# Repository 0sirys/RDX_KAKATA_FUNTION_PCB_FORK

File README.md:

# RDX_KAKATA_FUNTION_PCB
RDX_KAKATA_FUNTION_PCB es el repositorio de diseno PCB de la tarjeta de control de funciones del proyecto RDX para la NASA

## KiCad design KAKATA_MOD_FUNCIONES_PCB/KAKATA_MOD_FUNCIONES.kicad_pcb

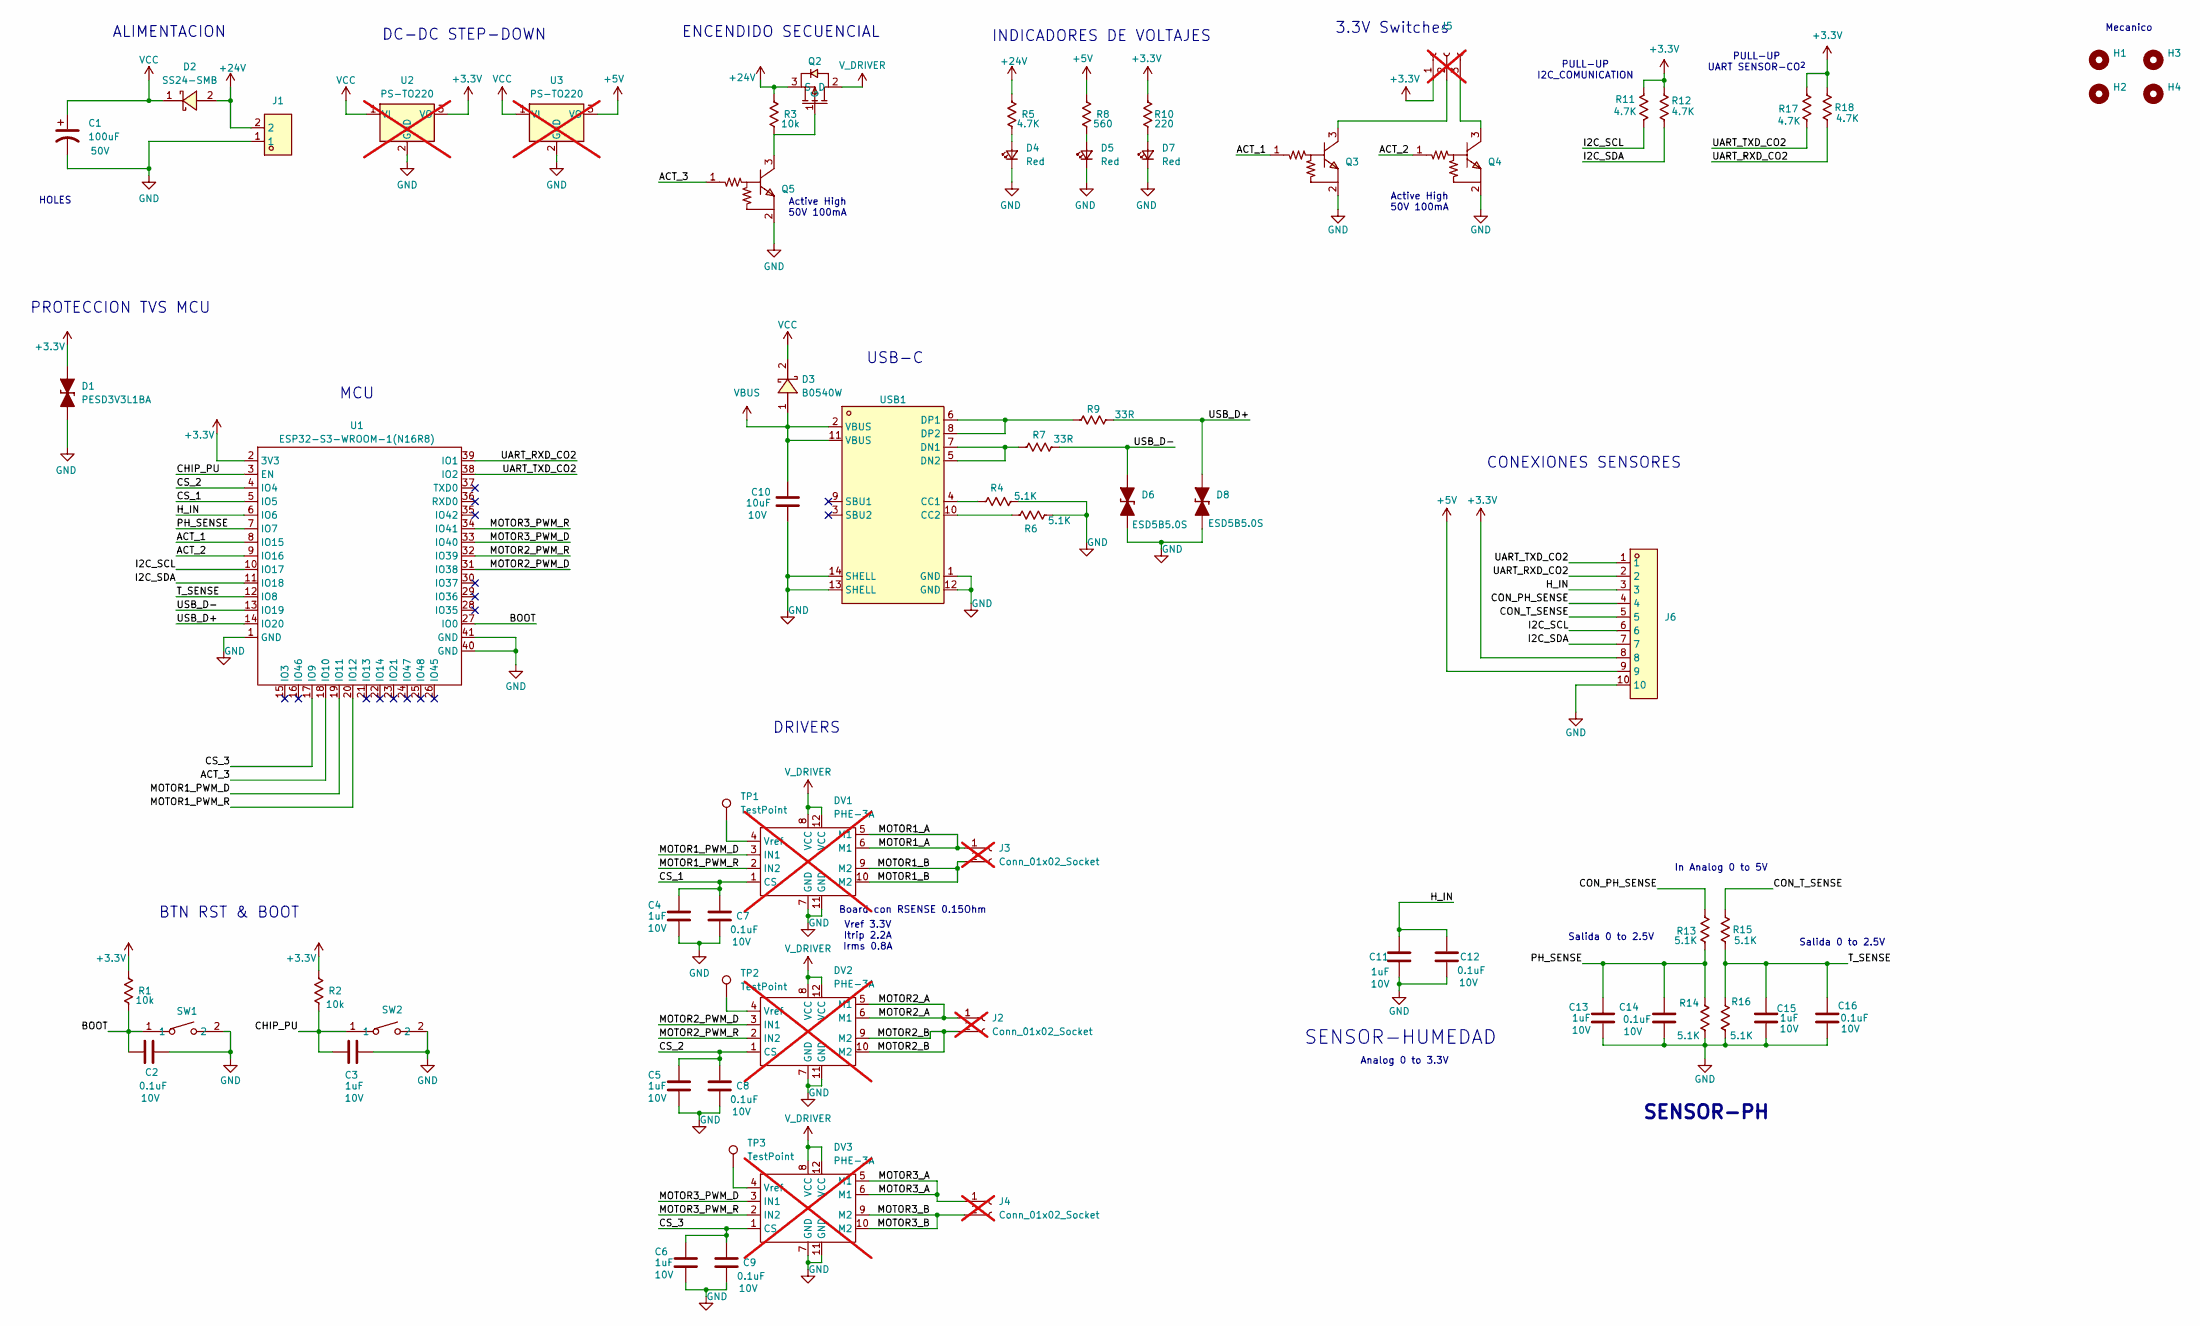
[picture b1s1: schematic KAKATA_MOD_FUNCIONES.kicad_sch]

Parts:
C1: 100uF; CAP-SMD_BD6.3-L6.6-W6.6-LS7.2-FD; LCSC Part C3151829
C2, C7, C8, C9, C12, C14, C16: 0.1uF; C0603; Voltage 10V; LCSC Part C14663
C3, C4, C5, C6, C11, C13, C15: 1uF; C0603; Voltage 10V; LCSC Part C113807
C10: 10uF; C0805; Voltage 10V; LCSC Part C88484
D1: PESD3V3L1BA; D_SOD-323
D2: SS24-SMB; SMB_L4.3-W3.6-LS5.3-RD; MPN SS24-SMB; LCSC Part C908683
D3: B0540W; SOD-123_L2.7-W1.6-LS3.7-FD; MPN B0540W; LCSC Part C7420325
D4, D5, D7: Red; LED_0201_0603Metric_Pad0.64x0.40mm_HandSolder; LCSC Part C965799
D6, D8: ESD5B5.0S; D_SOD-523; LCSC Part C93623
DV1, DV2, DV3: PHE-3A; not fitted
H1, H2, H3, H4: MountingHole; MountingHole_2.2mm_M2
J1: DB128L-5.08-2P-BK-S; CONN-TH_2P-P5.08_DB128L-5.08-2P-BK-S; LCSC Part C430601
J2, J3, J4: Conn_01x02_Socket; Molex_KK-254_AE-6410-02A_1x02_P2.54mm_Vertical; not fitted
J5: Conn_01x03_Socket; Molex_KK-254_AE-6410-03A_1x03_P2.54mm_Vertical; not fitted
J6: DB125-2.54-10P-GN; CONN-TH_DB125-2.54-10P-GN; LCSC Part C918128
Q2: AOD4185_C400894; TO-252-3_L6.6-W6.1-P4.57-LS9.9-BR-CW; MPN AOD4185; LCSC Part C400894
Q3, Q4, Q5: MMUN2215LT1G; SOT-23-3_L2.9-W1.3-P1.90-LS2.4-BR; MPN MMUN2215LT1G; LCSC Part C232613
R1, R2, R3: 10k; R0603; LCSC Part C98220
R4, R6, R13, R14, R15, R16: 5.1K; R0603; LCSC Part C105580
R5, R11, R12, R17, R18: 4.7K; R0603; LCSC Part C99782
R7, R9: 33R; R0603; LCSC Part C126353
R8: 560; R0603; LCSC Part C114629
R10: 220; R0603; LCSC Part C107696
SW1, SW2: TS-1088-AR02016; SW-SMD_L3.9-W3.0-P4.45; MPN TS-1088-AR02016; LCSC Part C720477
TP1, TP2, TP3: TestPoint; TestPoint_Pad_D2.0mm
U1: ESP32-S3-WROOM-1(N16R8); WIRELM-SMD_ESP32-S3-WROOM-1; LCSC Part C2913204
U2, U3: PS-TO220; PS-TO-220-3_Vertical; not fitted
USB1: TYPE-C 16PIN 2MD; USB-C-SMD_TYPE-C-6PIN-2MD-073; MPN TYPE-C 16PIN 2MD(073); LCSC Part C2765186

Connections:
+3.3V: D1.2 (A), J5.1, J6.8, R1.1, R2.1, R10.1, R11.1, R12.1, R17.1, R18.1, U1.2 (3V3), U2.3 (VO)
+5V: J6.9, R8.1, U3.3 (VO)
+24V: D2.2, J1.2, Q2.3 (S), R3.1, R5.1
/ACT_1: Q3.1, U1.8 (IO15)
/ACT_2: Q4.1, U1.9 (IO16)
/ACT_3: Q5.1, U1.18 (IO10)
/BOOT: C2.1, R1.2, SW1.1, U1.27 (IO0)
/CHIP_PU: C3.2, R2.2, SW2.1, U1.3 (EN)
/CON_PH_SENSE: J6.4, R13.1
/CON_T_SENSE: J6.5, R15.1
/CS_1: C4.2, C7.1, DV1.1 (CS), U1.5 (IO5)
/CS_2: C5.2, C8.1, DV2.1 (CS), U1.4 (IO4)
/CS_3: C6.2, C9.1, DV3.1 (CS), U1.17 (IO9)
/H_IN: C11.2, C12.1, J6.3, U1.6 (IO6)
/I2C_SCL: J6.6, R11.2, U1.10 (IO17)
/I2C_SDA: J6.7, R12.2, U1.11 (IO18)
/MOTOR1_A: DV1.5 (M1), DV1.6 (M1), J3.1
/MOTOR1_B: DV1.9 (M2), DV1.10 (M2), J3.2
/MOTOR1_PWM_D: DV1.3 (IN1), U1.19 (IO11)
/MOTOR1_PWM_R: DV1.2 (IN2), U1.20 (IO12)
/MOTOR2_A: DV2.5 (M1), DV2.6 (M1), J2.1
/MOTOR2_B: DV2.9 (M2), DV2.10 (M2), J2.2
/MOTOR2_PWM_D: DV2.3 (IN1), U1.31 (IO38)
/MOTOR2_PWM_R: DV2.2 (IN2), U1.32 (IO39)
/MOTOR3_A: DV3.5 (M1), DV3.6 (M1), J4.1
/MOTOR3_B: DV3.9 (M2), DV3.10 (M2), J4.2
/MOTOR3_PWM_D: DV3.3 (IN1), U1.33 (IO40)
/MOTOR3_PWM_R: DV3.2 (IN2), U1.34 (IO41)
/PH_SENSE: C13.2, C14.2, R13.2, R14.1, U1.7 (IO7)
/T_SENSE: C15.2, C16.2, R15.2, R16.1, U1.12 (IO8)
/UART_RXD_CO2: J6.2, R18.2, U1.39 (IO1)
/UART_TXD_CO2: J6.1, R17.2, U1.38 (IO2)
/USB_D+: D8.2 (A), R9.2, U1.14 (IO20)
/USB_D-: D6.2 (A), R7.2, U1.13 (IO19)
GND: C1.2, C2.2, C3.1, C4.1, C5.1, C6.1, C7.2, C8.2, C9.2, C10.2, C11.1, C12.2, C13.1, C14.1, C15.1, C16.1, D1.1 (K), D4.1 (K), D5.1 (K), D6.1 (K), D7.1 (K), D8.1 (K), DV1.7 (GND), DV1.11 (GND), DV2.7 (GND), DV2.11 (GND), DV3.7 (GND), DV3.11 (GND), J1.1, J6.10, Q3.2, Q4.2, Q5.2, R4.2, R6.2, R14.2, R16.2, SW1.2, SW2.2, U1.1 (GND), U1.40 (GND), U1.41 (GND), U2.2 (GND), U3.2 (GND), USB1.1 (GND), USB1.12 (GND), USB1.13 (SHELL), USB1.14 (SHELL)
unnamed: D4.2 (A), R5.2
unnamed: D5.2 (A), R8.2
unnamed: D7.2 (A), R10.2
unnamed: DV1.4 (Vref), TP1.1 (1_1)
unnamed: DV2.4 (Vref), TP2.1 (1_1)
unnamed: DV3.4 (Vref), TP3.1 (1_1)
unnamed: J5.2, Q3.3
unnamed: J5.3, Q4.3
unnamed: Q2.1 (G), Q5.3, R3.2
unnamed: R4.1, USB1.4 (CC1)
unnamed: R6.1, USB1.10 (CC2)
unnamed: R7.1, USB1.5 (DN2), USB1.7 (DN1)
unnamed: R9.1, USB1.6 (DP1), USB1.8 (DP2)
VBUS: C10.1, D3.1, USB1.2 (VBUS), USB1.11 (VBUS)
VCC: C1.1, D2.1, D3.2, U2.1 (VI), U3.1 (VI)
V_DRIVER: DV1.8 (VCC), DV1.12 (VCC), DV2.8 (VCC), DV2.12 (VCC), DV3.8 (VCC), DV3.12 (VCC), Q2.2 (D)

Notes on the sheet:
3.3V Switches
Analog 0 to 3.3V
Active High 50V 100mA
USB-C
Salida 0 to 2.5V
ENCENDIDO SECUENCIAL
SENSOR-PH
PULL-UP UART SENSOR-CO^{2}
HOLES
SENSOR-HUMEDAD
ALIMENTACION
DRIVERS
INDICADORES DE VOLTAJES
MCU
PROTECCION TVS MCU
Vref 3.3V Itrip 2.2A Irms 0.8A
PULL-UP I2C_COMUNICATION
Board con RSENSE 0.15Ohm
Mecanico
In Analog 0 to 5V
CONEXIONES SENSORES
BTN RST & BOOT
DC-DC STEP-DOWN

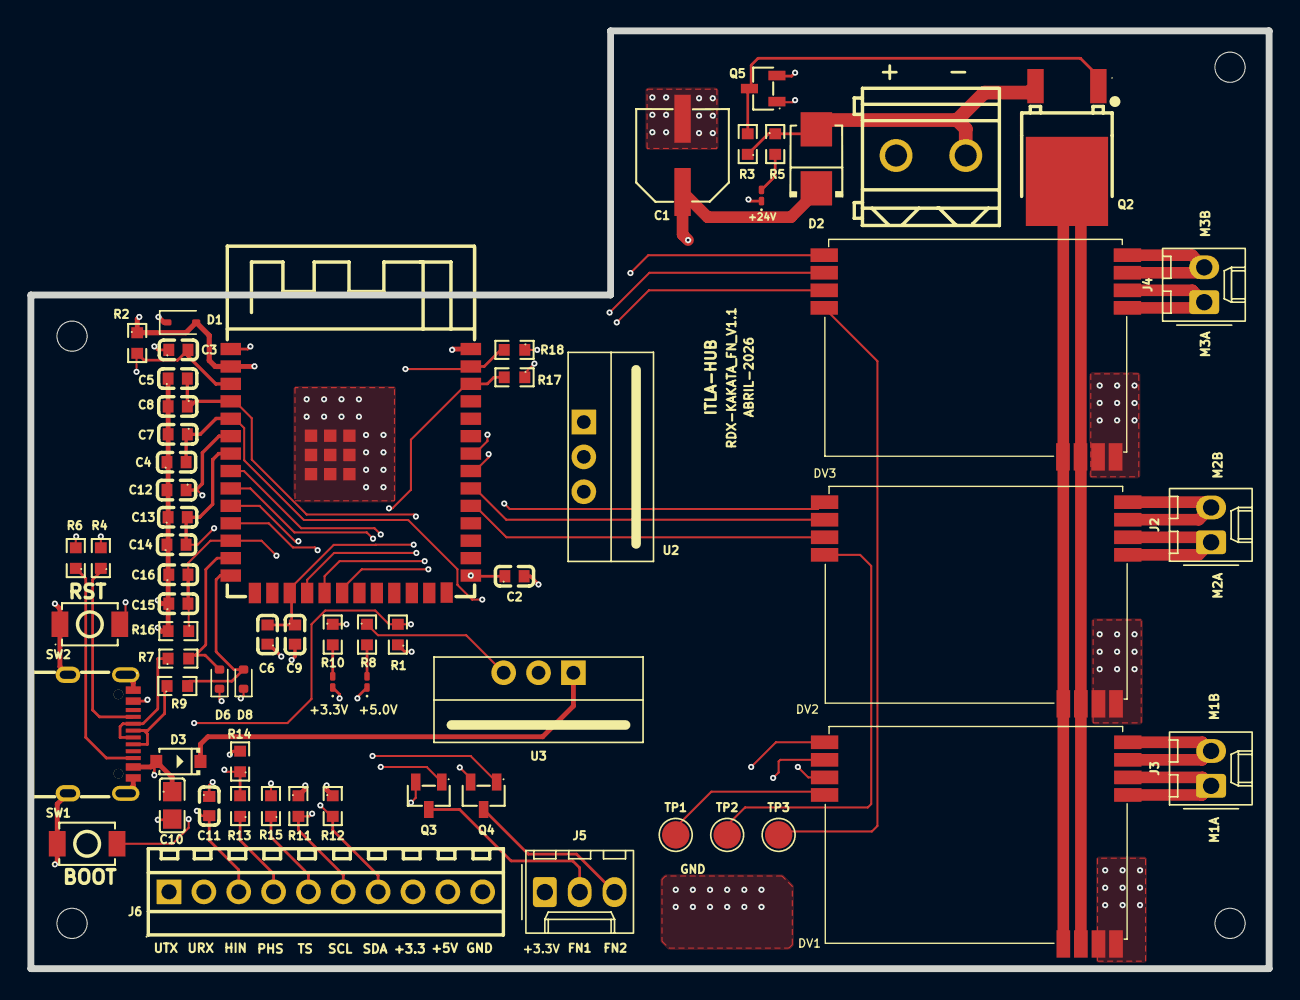
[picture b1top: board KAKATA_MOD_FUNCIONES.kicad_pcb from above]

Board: 4 copper layers, 90.2 x 68.3 mm, 68 parts (0 on the bottom side), 51 nets.

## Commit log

2026-03-06 Version RC1 Componentes verificados y BOM terminados
2026-04-26 Btn's BOOT y RST agregados. Encendido secuencial implementado
